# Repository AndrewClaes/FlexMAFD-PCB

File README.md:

# FlexMAFD-PCB
A basic PCB for the FlexMAFD device by dimant / FlexMAFD

https://github.com/dimant/FlexMAFD

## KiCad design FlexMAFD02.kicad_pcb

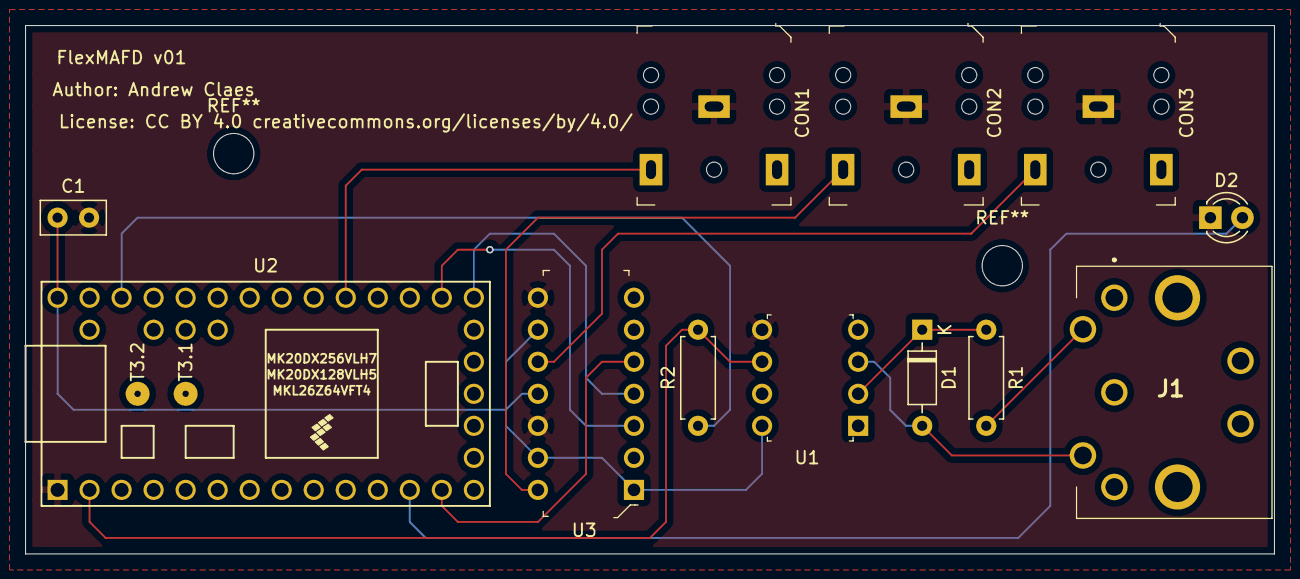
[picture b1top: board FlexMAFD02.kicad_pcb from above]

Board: 2 copper layers, 99.1 x 41.9 mm, 12 parts (0 on the bottom side), 14 nets.

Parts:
C1: 0.1uF; C_Disc_D5.0mm_W2.5mm_P2.50mm
CON1, CON2, CON3: SJ1-3523N; Headphone_Jack_3.5mm_SJ1-3523N
D1: 1N4148; D_DO-35_SOD27_P7.62mm_Horizontal
D2: LED; LED_D3.0mm
J1: 57PC5F
R1: 220; R_Axial_DIN0207_L6.3mm_D2.5mm_P7.62mm_Horizontal
R2: 470; R_Axial_DIN0207_L6.3mm_D2.5mm_P7.62mm_Horizontal
U1: 6N138; DIP-8_W7.62mm
U2: Teensy-LC; Teensy30_31_32_LC
U3: MCP4902; DIP-14_W3mm

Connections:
Earth: C1.2, CON1.1, CON2.1, CON3.1, D2.1, U1.5, U2.1, U3.8, U3.12
unnamed: C1.1, U1.8, U2.33, U3.1, U3.9, U3.11, U3.13
unnamed: CON1.2, U2.24
unnamed: CON2.2, U3.14
unnamed: CON3.2, U3.10
unnamed: D1.1, R1.1, U1.2
unnamed: D1.2, J1.5, U1.3
unnamed: D2.2, U2.12
unnamed: J1.4, R1.2
unnamed: R2.1, U2.31
unnamed: R2.2, U1.6, U2.2
unnamed: U2.13, U3.5
unnamed: U2.20, U3.4
unnamed: U2.21, U3.3

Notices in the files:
FlexMAFD02.kicad_pcb:
License: CC BY 4.0 creativecommons.org/licenses/by/4.0
